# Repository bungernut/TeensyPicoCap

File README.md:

# TeensyPicoCap

| LOC | Part | Digikey |
| --- | ---  | --- |
| C2  | 4.7uF | 399-C0805C475K4RAC7210CT-ND |
| C3  | 10uF  | 1276-1764-1-ND |
| C4  | 0.1uF | 399-C320C104K5R5TA7305CT-ND |
| C5  | 10nF C0G | 1292-0805N103J500CT-ND | 
| C6 | 47uF | 1276-3063-1-ND | 
| F1 | 500mA Polyfuse | F2112CT-ND | 
|J1-J3 | 2p Term Block | 2057-EBWA-02-B-ND | 
| J9 | RJ45 | 1278-1052-ND |
| J16 | Barrel Jack | CP-002A-ND | 
| R1 | 1k Ref |  |
| R2 | 1k RTD | 223-1807-ND | 
| U1 | PicoCap04 | Mouser: PCAP04-BQFM-24 |

https://www.digikey.com/short/n2d7w2qm

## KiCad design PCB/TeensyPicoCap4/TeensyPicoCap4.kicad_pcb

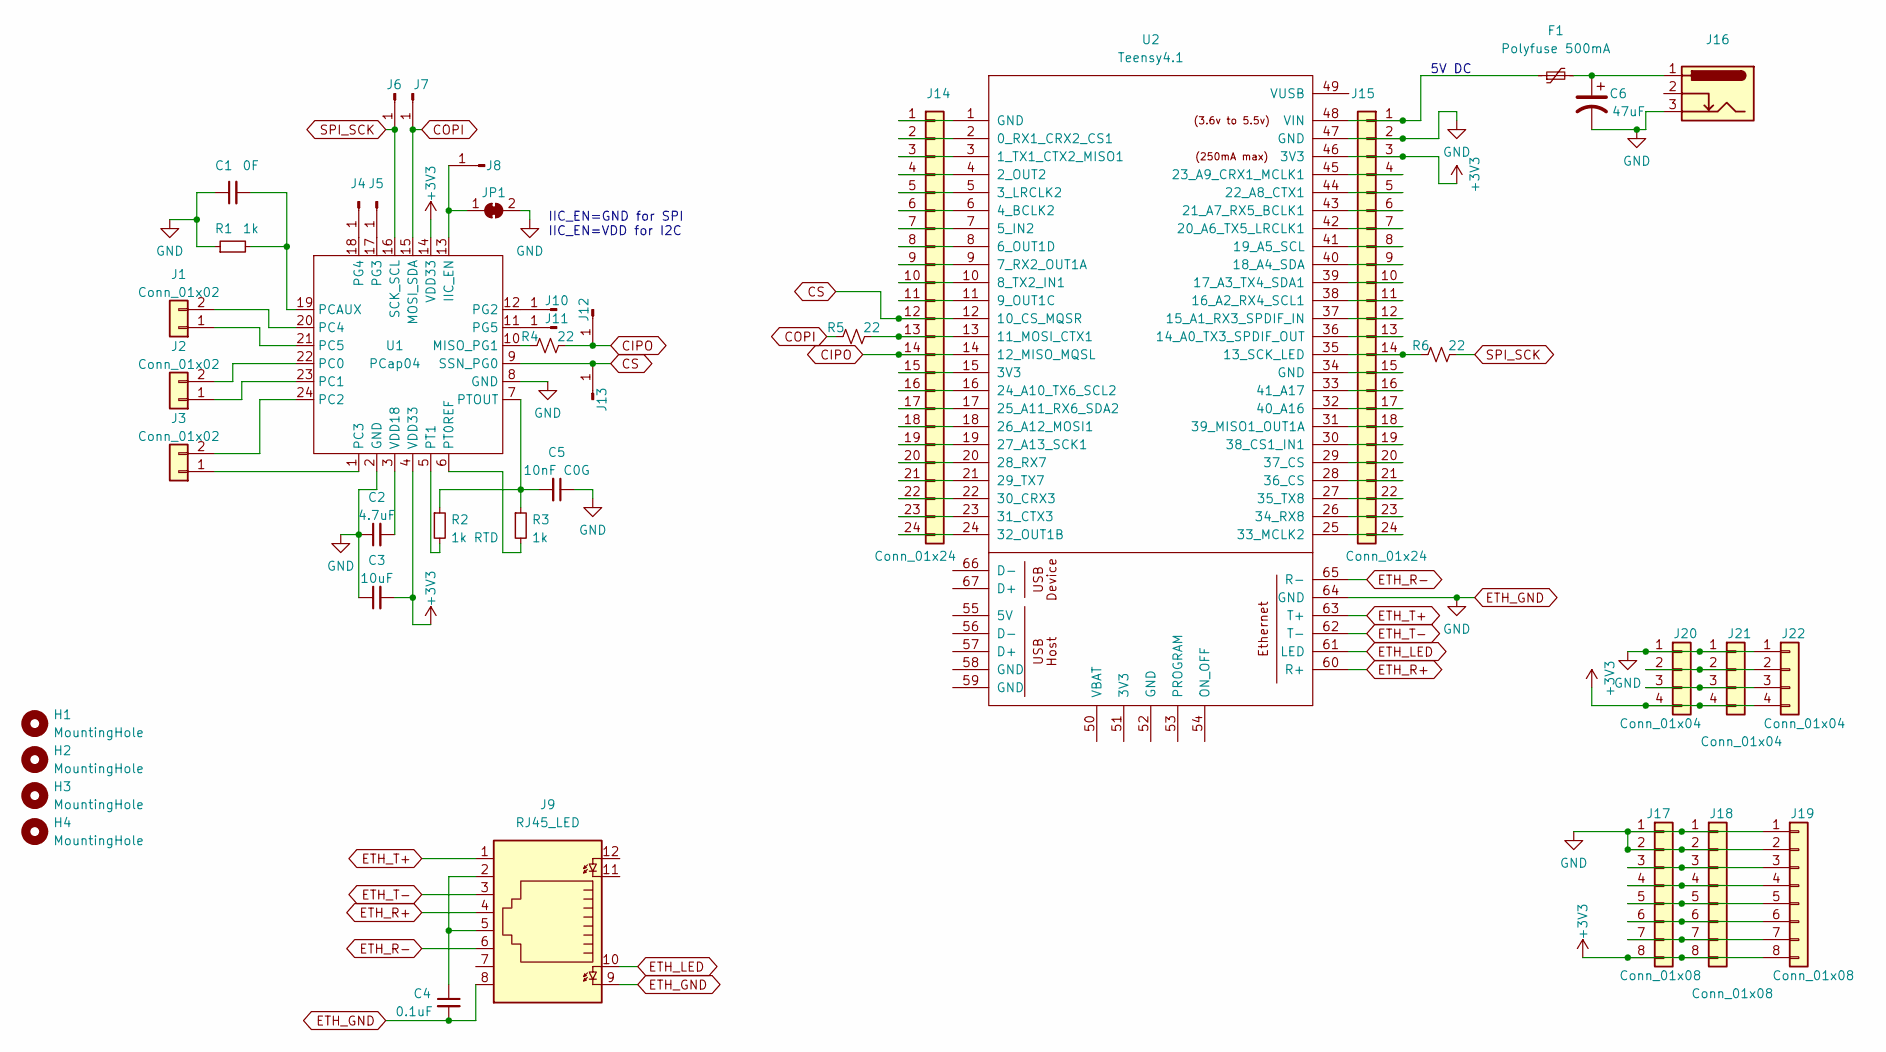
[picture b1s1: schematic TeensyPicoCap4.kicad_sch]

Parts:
C1: 0F; C_Axial_L5.1mm_D3.1mm_P12.50mm_Horizontal
C2: 4.7uF; C_0805_2012Metric_Pad1.18x1.45mm_HandSolder; Digikey 399-C0805C475K4RAC7210CT-ND
C3: 10uF; C_0805_2012Metric_Pad1.18x1.45mm_HandSolder; Digikey 1276-1764-1-ND
C4: 0.1uF; C_Disc_D3.0mm_W1.6mm_P2.50mm; Digikey 399-C320C104K5R5TA7305CT-ND
C5: 10nF C0G; C_0805_2012Metric_Pad1.18x1.45mm_HandSolder; Digikey 1292-0805N103J500CT-ND
C6: 47uF; C_1206_3216Metric_Pad1.33x1.80mm_HandSolder; Digikey 1276-3063-1-ND
F1: Polyfuse 500mA; Fuse_1206_3216Metric_Pad1.42x1.75mm_HandSolder; Digikey F2112CT-ND
H1, H2, H3, H4: MountingHole; MountingHole_3.2mm_M3
J1, J2, J3: Conn_01x02; PhoenixContact_MCV_1,5_2-G-3.81_1x02_P3.81mm_Vertical; Digikey 2057-EBWA-02-B-ND
J4, J6, J8, J10, J11, J12, J13: Conn_01x01_Male; SolderWire-0.5sqmm_1x01_D0.9mm_OD2.1mm
J5, J7: con; SolderWire-0.5sqmm_1x01_D0.9mm_OD2.1mm
J9: RJ45_LED; RJ45_Cetus_J1B1211CCD_Horizontal; Digikey 1278-1052-ND
J14, J15: Conn_01x24; PinHeader_1x24_P2.54mm_Vertical
J16: Barrel_Jack_Switch_Pin3Ring; BarrelJack_Horizontal; Digikey CP-002A-ND
J17, J18, J19: Conn_01x08; PinHeader_1x08_P2.54mm_Vertical
J20, J21, J22: Conn_01x04; PinHeader_1x04_P2.54mm_Vertical
JP1: SolderJumper_2_Bridged; SolderJumper-2_P1.3mm_Bridged_RoundedPad1.0x1.5mm
R1: 1k; R_Axial_DIN0411_L9.9mm_D3.6mm_P12.70mm_Horizontal
R2: 1k RTD; R_Axial_DIN0204_L3.6mm_D1.6mm_P1.90mm_Vertical; Digikey 223-1807-ND
R3: 1k; R_Axial_DIN0309_L9.0mm_D3.2mm_P12.70mm_Horizontal; Digikey 273-MOX70031001BZE-ND
R4, R5, R6: 22; R_0805_2012Metric_Pad1.20x1.40mm_HandSolder
U1: PCap04; QFN-24-1EP_4x4mm_P0.5mm_EP2.6x2.6mm
U2: Teensy4.1; Teensy41

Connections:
+3V3: C3.2, J15.3, J17.8, J18.8, J19.8, J20.4, J21.4, J22.4, U1.4 (VDD33), U1.14 (VDD33), U2.46 (3V3)
CIPO: J12.1, J14.14, R4.2, U2.14 (12_MISO_MQSL)
COPI: J7.1, R5.1, U1.15 (MOSI_SDA)
CS: J13.1, J14.12, U1.9 (SSN_PG0), U2.12 (10_CS_MQSR)
ETH_GND: C1.1, C2.1, C3.1, C4.2, C5.1, C6.2, J9.8, J9.9, J15.2, J16.3, J17.1, J17.2, J18.1, J18.2, J19.1, J19.2, J20.1, J21.1, J22.1, JP1.2 (B), R1.1, U1.2 (GND), U1.8 (GND), U2.47 (GND), U2.64 (GND)
ETH_LED: J9.10, U2.61 (LED)
ETH_R+: J9.4, U2.60 (R+)
ETH_R-: J9.6, U2.65 (R-)
ETH_T+: J9.1, U2.63 (T+)
ETH_T-: J9.3, U2.62 (T-)
unnamed: C1.2, R1.2, U1.19 (PCAUX)
unnamed: C2.2, U1.3 (VDD18)
unnamed: C4.1, J9.2, J9.5
unnamed: C5.2, R2.1, R3.1, U1.7 (PTOUT)
unnamed: C6.1, F1.2, J16.1
unnamed: F1.1, J15.1, U2.48 (VIN)
unnamed: J1.1, U1.21 (PC5)
unnamed: J1.2, U1.20 (PC4)
unnamed: J2.1, U1.23 (PC1)
unnamed: J2.2, U1.22 (PC0)
unnamed: J3.1, U1.1 (PC3)
unnamed: J3.2, U1.24 (PC2)
unnamed: J4.1, U1.18 (PG4)
unnamed: J5.1, U1.17 (PG3)
unnamed: J8.1, JP1.1 (A), U1.13 (IIC_EN)
unnamed: J10.1, U1.12 (PG2)
unnamed: J11.1, U1.11 (PG5)
unnamed: J14.1, U2.1 (GND)
unnamed: J14.2, U2.2 (0_RX1_CRX2_CS1)
unnamed: J14.3, U2.3 (1_TX1_CTX2_MISO1)
unnamed: J14.4, U2.4 (2_OUT2)
unnamed: J14.5, U2.5 (3_LRCLK2)
unnamed: J14.6, U2.6 (4_BCLK2)
unnamed: J14.7, U2.7 (5_IN2)
unnamed: J14.8, U2.8 (6_OUT1D)
unnamed: J14.9, U2.9 (7_RX2_OUT1A)
unnamed: J14.10, U2.10 (8_TX2_IN1)
unnamed: J14.11, U2.11 (9_OUT1C)
unnamed: J14.13, R5.2, U2.13 (11_MOSI_CTX1)
unnamed: J14.15, U2.15 (3V3)
unnamed: J14.16, U2.16 (24_A10_TX6_SCL2)
unnamed: J14.17, U2.17 (25_A11_RX6_SDA2)
unnamed: J14.18, U2.18 (26_A12_MOSI1)
unnamed: J14.19, U2.19 (27_A13_SCK1)
unnamed: J14.20, U2.20 (28_RX7)
unnamed: J14.21, U2.21 (29_TX7)
unnamed: J14.22, U2.22 (30_CRX3)
unnamed: J14.23, U2.23 (31_CTX3)
unnamed: J14.24, U2.24 (32_OUT1B)
unnamed: J15.4, U2.45 (23_A9_CRX1_MCLK1)
unnamed: J15.5, U2.44 (22_A8_CTX1)
unnamed: J15.6, U2.43 (21_A7_RX5_BCLK1)
unnamed: J15.7, U2.42 (20_A6_TX5_LRCLK1)
unnamed: J15.8, U2.41 (19_A5_SCL)
unnamed: J15.9, U2.40 (18_A4_SDA)
unnamed: J15.10, U2.39 (17_A3_TX4_SDA1)
unnamed: J15.11, U2.38 (16_A2_RX4_SCL1)
unnamed: J15.12, U2.37 (15_A1_RX3_SPDIF_IN)
unnamed: J15.13, U2.36 (14_A0_TX3_SPDIF_OUT)
unnamed: J15.14, R6.1, U2.35 (13_SCK_LED)
unnamed: J15.15, U2.34 (GND)
unnamed: J15.16, U2.33 (41_A17)
unnamed: J15.17, U2.32 (40_A16)
unnamed: J15.18, U2.31 (39_MISO1_OUT1A)
unnamed: J15.19, U2.30 (38_CS1_IN1)
unnamed: J15.20, U2.29 (37_CS)
unnamed: J15.21, U2.28 (36_CS)
unnamed: J15.22, U2.27 (35_TX8)
unnamed: J15.23, U2.26 (34_RX8)
unnamed: J15.24, U2.25 (33_MCLK2)
unnamed: J17.3, J18.3, J19.3
unnamed: J17.4, J18.4, J19.4
unnamed: J17.5, J18.5, J19.5
unnamed: J17.6, J18.6, J19.6
unnamed: J17.7, J18.7, J19.7
unnamed: J20.2, J21.2, J22.2
unnamed: J20.3, J21.3, J22.3
unnamed: R2.2, U1.5 (PT1)
unnamed: R3.2, U1.6 (PT0REF)
unnamed: R4.1, U1.10 (MISO_PG1)
SPI_SCK: J6.1, R6.2, U1.16 (SCK_SCL)

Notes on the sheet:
5V DC
IIC_EN=GND for SPI IIC_EN=VDD for I2C

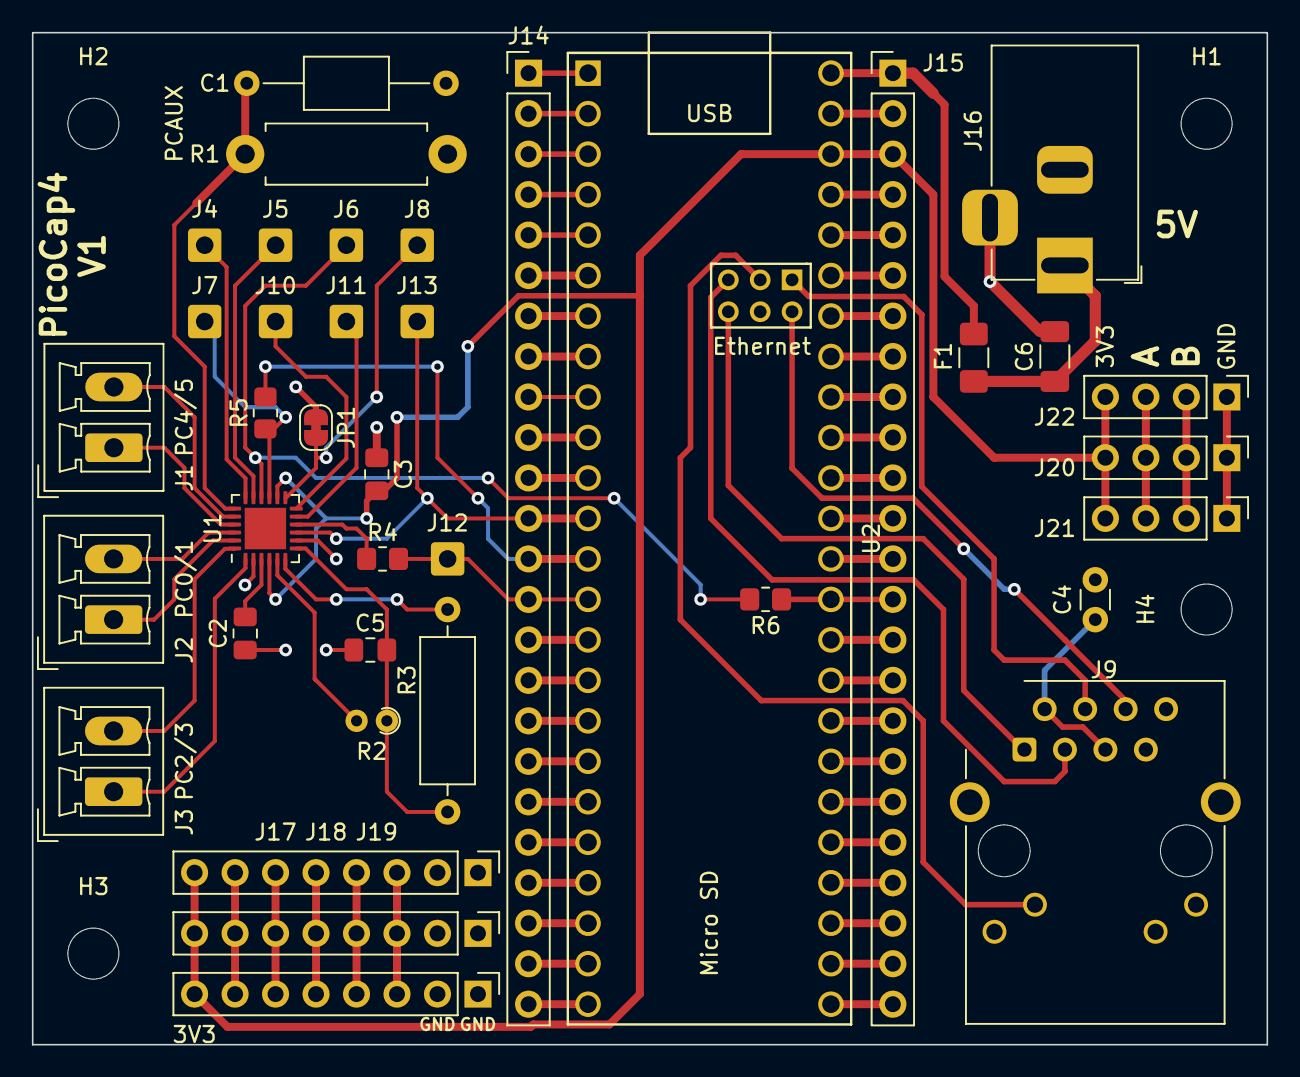
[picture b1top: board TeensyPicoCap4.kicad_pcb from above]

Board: 2 copper layers, 77.5 x 63.5 mm, 42 parts (0 on the bottom side), 81 nets.

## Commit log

2022-08-18 initial commit, still working on sch
2022-08-26 first design
2022-08-26 remove temp work
2022-08-27 submitted V1 w/ more silk and digikey parts
